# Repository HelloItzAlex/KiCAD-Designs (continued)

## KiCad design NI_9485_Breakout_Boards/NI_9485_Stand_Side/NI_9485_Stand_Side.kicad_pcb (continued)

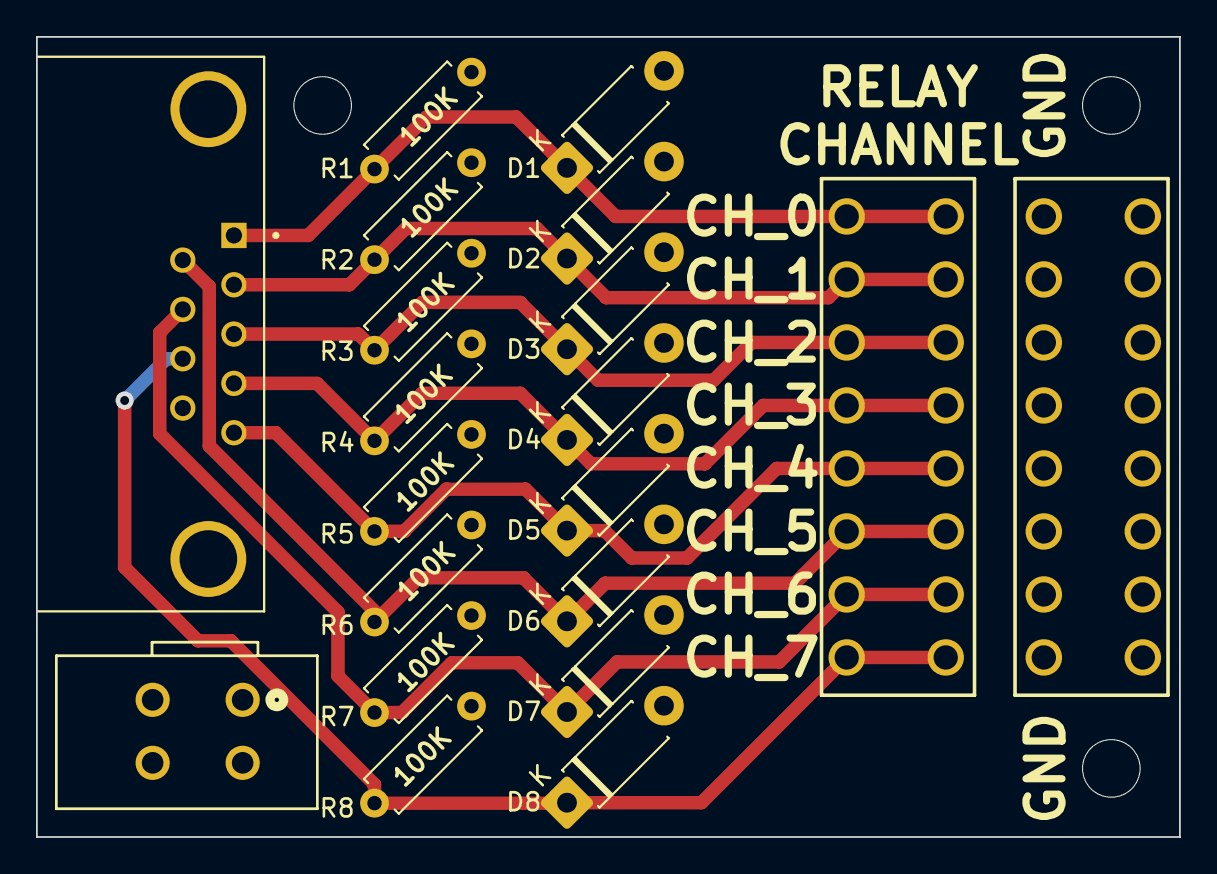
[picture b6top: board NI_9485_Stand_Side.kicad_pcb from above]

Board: 2 copper layers, 63.5 x 44.4 mm, 23 parts (0 on the bottom side), 9 nets.

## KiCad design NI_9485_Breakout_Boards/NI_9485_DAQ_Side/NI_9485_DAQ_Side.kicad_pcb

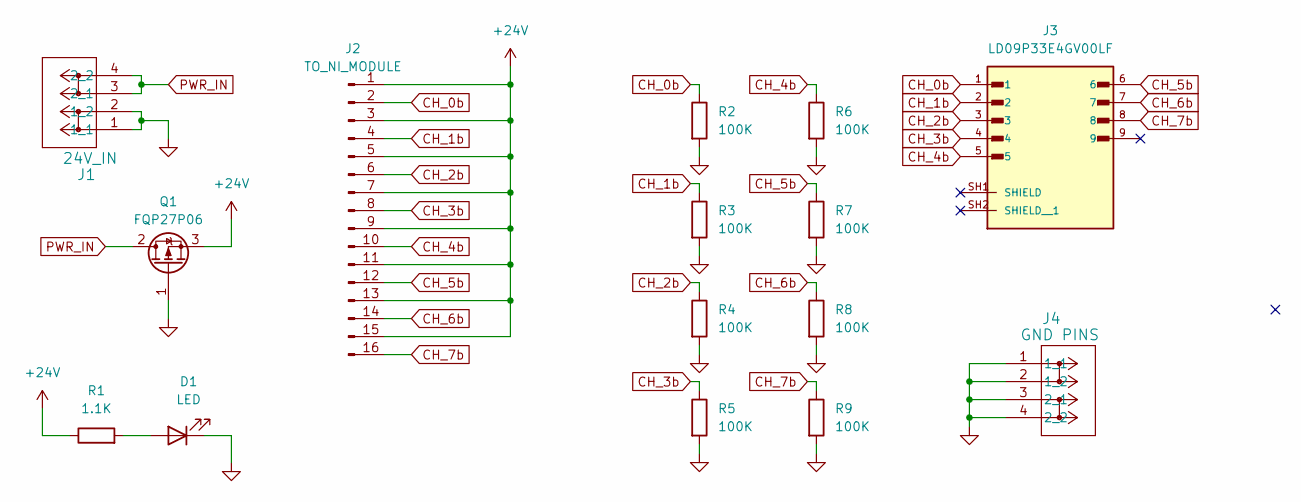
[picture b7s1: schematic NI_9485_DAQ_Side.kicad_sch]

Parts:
D1: LED; LED_D3.0mm_FlatTop
J1: 24V_IN; CONN2_2601-1102_WAG
J2: TO_NI_MODULE; 01x16 Horiz Pins
J3: LD09P33E4GV00LF; AMPHENOL_LD09P33E4GV00LF; PARTREV B
J4: GND PINS; CONN2_2601-1102_WAG
Q1: FQP27P06; TO-220-3_Vertical
R1: 1.1K; R_Axial_DIN0207_L6.3mm_D2.5mm_P7.62mm_Horizontal
R2, R3, R4, R5, R6, R7, R8, R9: 100K; R_Axial_DIN0207_L6.3mm_D2.5mm_P7.62mm_Horizontal

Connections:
+24V: J2.1, J2.3, J2.5, J2.7, J2.9, J2.11, J2.13, J2.15, Q1.3 (S), R1.1
CH_0b: J2.2, J3.1, R2.1
CH_1b: J2.4, J3.2, R3.1
CH_2b: J2.6, J3.3, R4.1
CH_3b: J2.8, J3.4, R5.1
CH_4b: J2.10, J3.5, R6.1
CH_5b: J2.12, J3.6, R7.1
CH_6b: J2.14, J3.7, R8.1
CH_7b: J2.16, J3.8, R9.1
GND: D1.1 (K), J1.1 (1_1), J1.2 (1_2), J4.1 (1_1), J4.2 (1_2), J4.3 (2_1), J4.4 (2_2), Q1.1 (G), R2.2, R3.2, R4.2, R5.2, R6.2, R7.2, R8.2, R9.2
unnamed: D1.2 (A), R1.2
PWR_IN: J1.3 (2_1), J1.4 (2_2), Q1.2 (D)

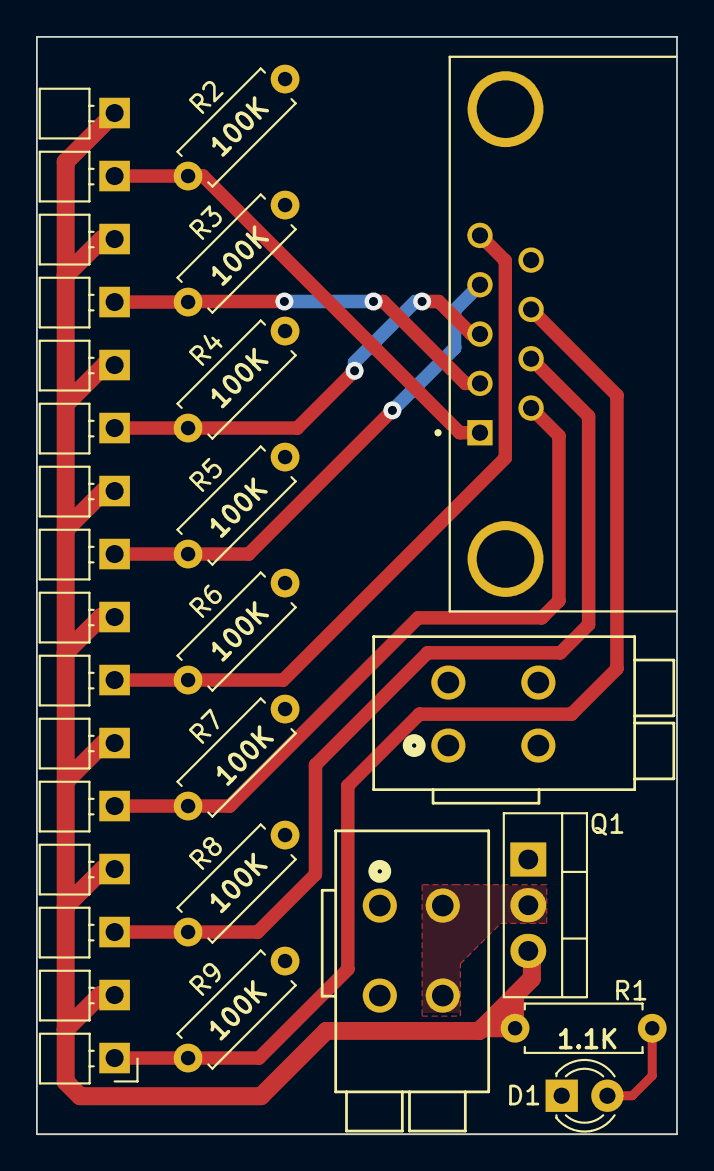
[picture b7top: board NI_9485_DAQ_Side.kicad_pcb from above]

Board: 2 copper layers, 35.6 x 61.0 mm, 15 parts (0 on the bottom side), 12 nets.

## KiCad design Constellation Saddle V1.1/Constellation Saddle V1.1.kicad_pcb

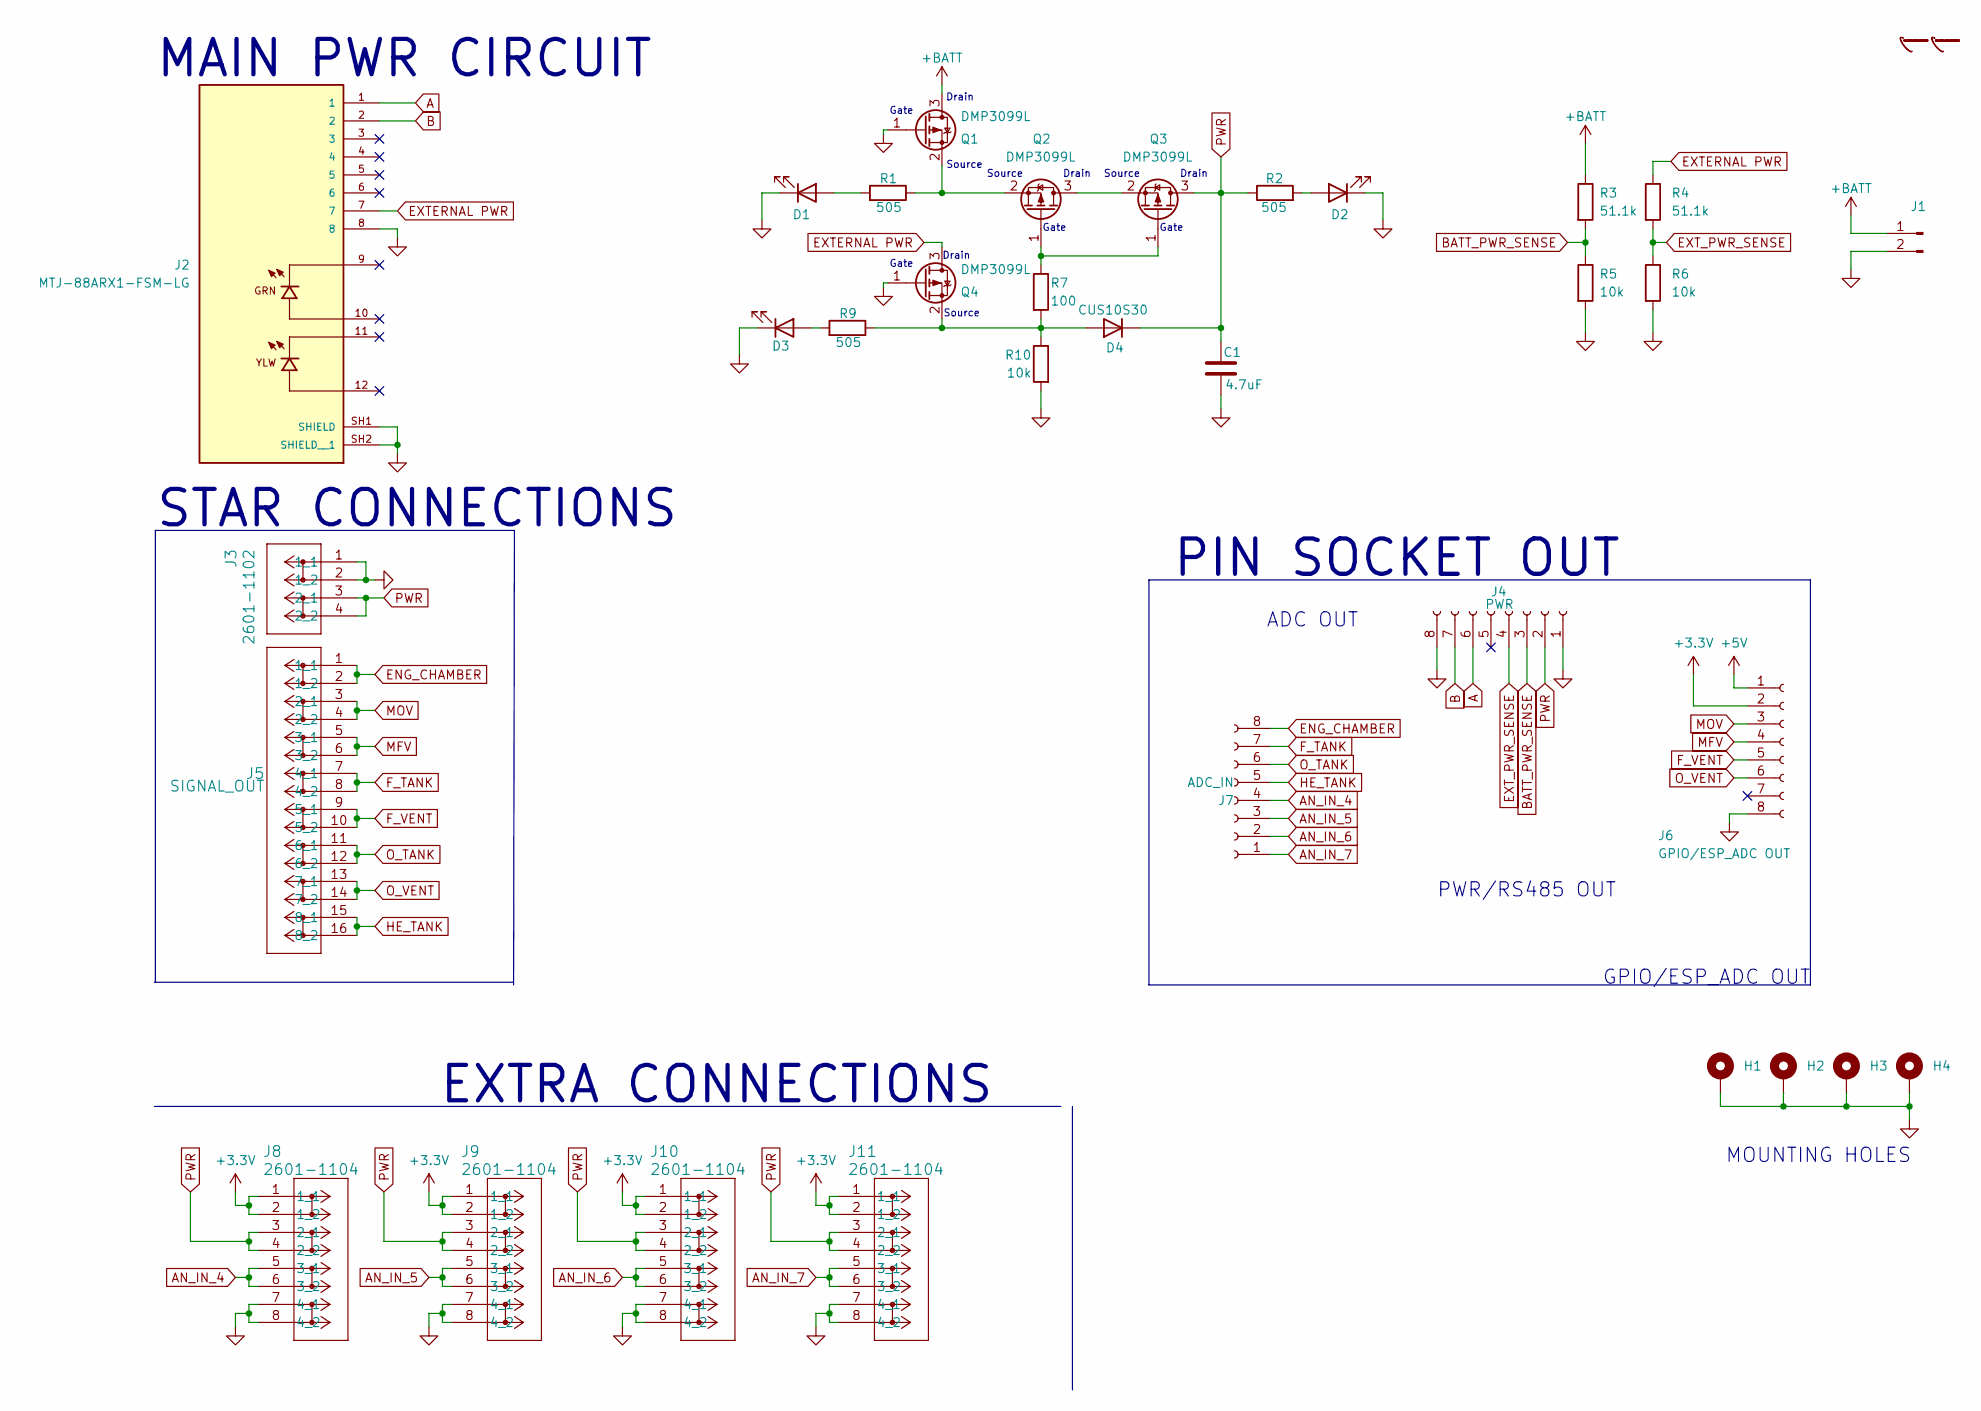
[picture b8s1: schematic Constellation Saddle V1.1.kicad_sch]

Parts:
C1: 4.7uF; C_0805_2012Metric
D1, D2, D3: LED; LED_0805_2012Metric
D4: CUS10S30; D_SOD-323
H1, H2, H3, H4: MountingHole_Pad; MountingHole_3.2mm_M3_DIN965_Pad
J1: Conn_01x02_Pin; SolderWire-0.75sqmm_1x02_P4.8mm_D1.25mm_OD2.3mm_Relief
J2: MTJ-88ARX1-FSM-LG; ADAMTECH_MTJ-88ARX1-FSM-LG; PARTREV H
J3: 2601-1102; CONN2_2601-1102_WAG
J4: PWR; PinSocket_1x08_P2.54mm_Vertical
J5: SIGNAL_OUT; CONN8_2601-1108_WAG
J6: GPIO/ESP_ADC OUT; PinSocket_1x08_P2.54mm_Vertical
J7: ADC_IN; PinSocket_1x08_P2.54mm_Vertical
J8, J9, J10, J11: 2601-1104; CONN4_2601-1104_WAG
Q1, Q2, Q3, Q4: DMP3099L; SOT-23-3
R1, R2, R9: 505; R_0805_2012Metric
R3, R4: 51.1k; R_0805_2012Metric
R5, R6, R10: 10k; R_0805_2012Metric
R7: 100; R_0805_2012Metric

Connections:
+3.3V: J6.2, J8.1 (1_1), J8.2 (1_2), J9.1 (1_1), J9.2 (1_2), J10.1 (1_1), J10.2 (1_2), J11.1 (1_1), J11.2 (1_2)
+5V: J6.1
+BATT: J1.1, Q1.3 (D), R3.1
A: J2.1, J4.6
AN_IN_4: J7.4, J8.5 (3_1), J8.6 (3_2)
AN_IN_5: J7.3, J9.5 (3_1), J9.6 (3_2)
AN_IN_6: J7.2, J10.5 (3_1), J10.6 (3_2)
AN_IN_7: J7.1, J11.5 (3_1), J11.6 (3_2)
B: J2.2, J4.7
BATT_PWR_SENSE: J4.3, R3.2, R5.1
ENG_CHAMBER: J5.1 (1_1), J5.2 (1_2), J7.8
EXTERNAL PWR: J2.7, Q4.3 (D), R4.1
EXT_PWR_SENSE: J4.4, R4.2, R6.1
F_TANK: J5.7 (4_1), J5.8 (4_2), J7.7
F_VENT: J5.9 (5_1), J5.10 (5_2), J6.5
GND: C1.2, D1.1 (K), D2.1 (K), D3.1 (K), H1.1, H2.1, H3.1, H4.1, J1.2, J2.8, J2.SH1 (SHIELD), J2.SH2 (SHIELD__1), J3.1 (1_1), J3.2 (1_2), J4.1, J4.8, J6.8, J8.7 (4_1), J8.8 (4_2), J9.7 (4_1), J9.8 (4_2), J10.7 (4_1), J10.8 (4_2), J11.7 (4_1), J11.8 (4_2), Q1.1 (G), Q4.1 (G), R5.2, R6.2, R10.2
HE_TANK: J5.15 (8_1), J5.16 (8_2), J7.5
MFV: J5.5 (3_1), J5.6 (3_2), J6.4
MOV: J5.3 (2_1), J5.4 (2_2), J6.3
unnamed: D1.2 (A), R1.2
unnamed: D2.2 (A), R2.2
unnamed: D3.2 (A), R9.2
unnamed: D4.2 (A), Q4.2 (S), R7.2, R9.1, R10.1
unnamed: Q1.2 (S), Q2.2 (S), R1.1
unnamed: Q2.3 (D), Q3.2 (S)
unnamed: Q2.1 (G), Q3.1 (G), R7.1
O_TANK: J5.11 (6_1), J5.12 (6_2), J7.6
O_VENT: J5.13 (7_1), J5.14 (7_2), J6.6
PWR: C1.1, D4.1 (K), J3.3 (2_1), J3.4 (2_2), J4.2, J8.3 (2_1), J8.4 (2_2), J9.3 (2_1), J9.4 (2_2), J10.3 (2_1), J10.4 (2_2), J11.3 (2_1), J11.4 (2_2), Q3.3 (D), R2.1

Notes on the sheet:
Gate
GPIO/ESP_ADC OUT
Drain
Source
MOUNTING HOLES
PWR/RS485 OUT
MAIN PWR CIRCUIT
ADC OUT
STAR CONNECTIONS
EXTRA CONNECTIONS
PIN SOCKET OUT

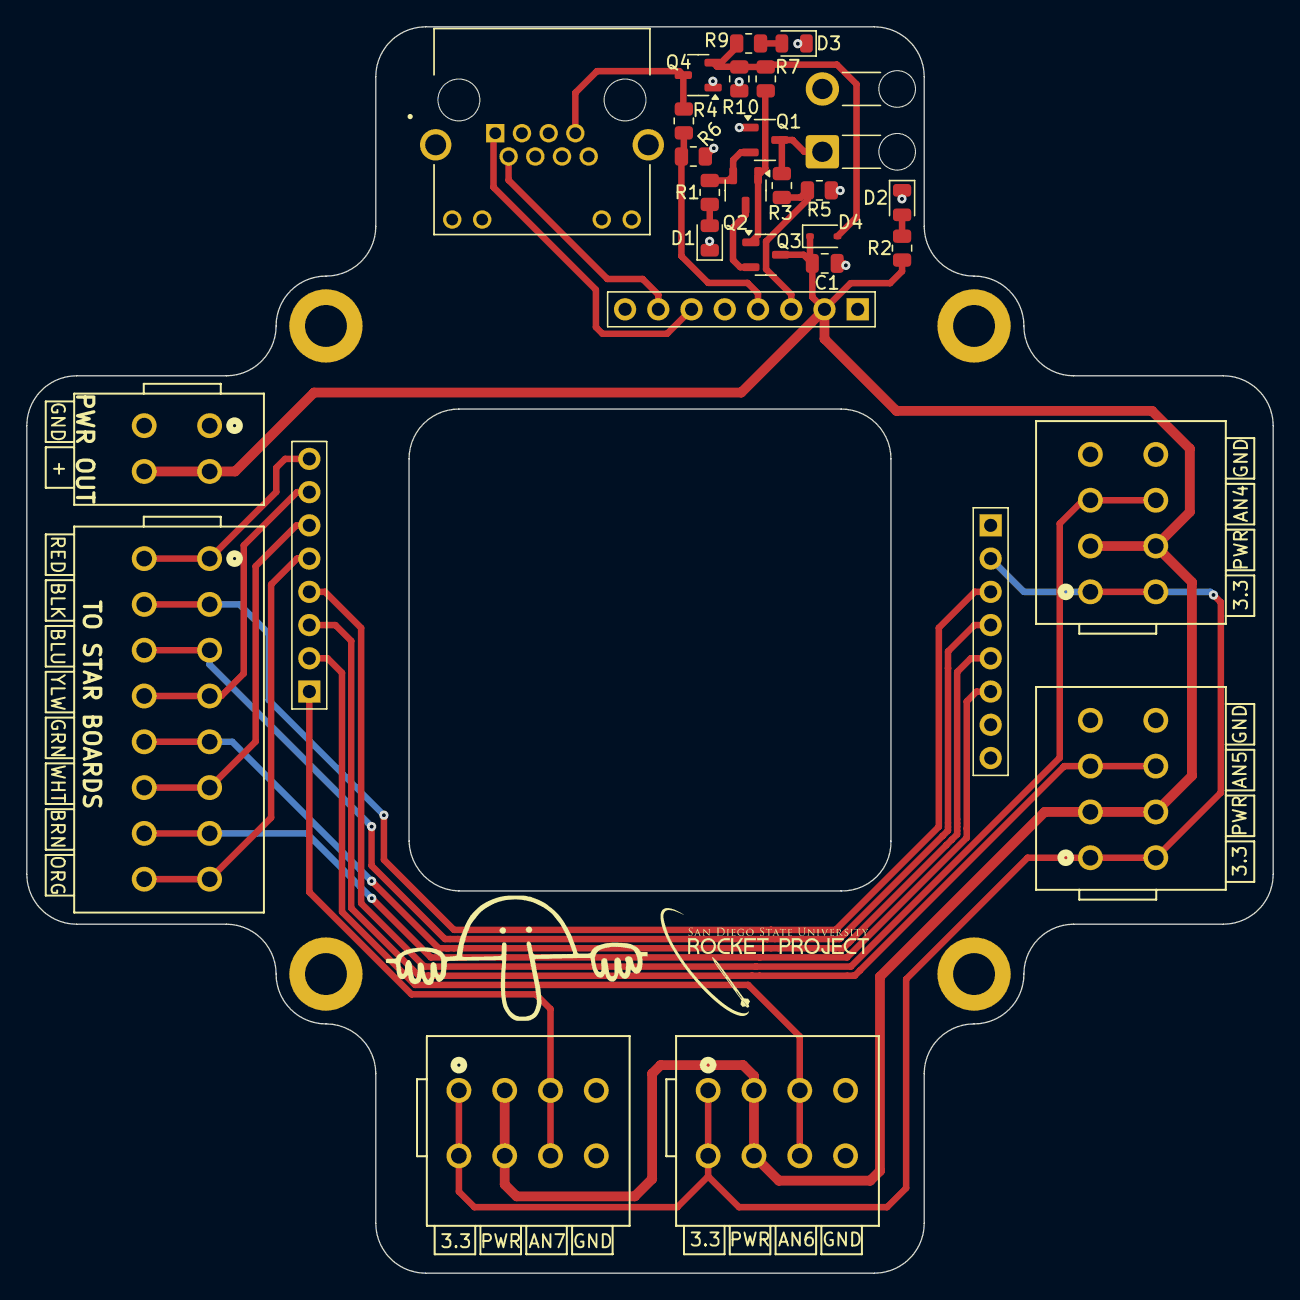
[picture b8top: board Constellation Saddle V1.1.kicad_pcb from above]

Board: 2 copper layers, 95.2 x 95.2 mm, 33 parts (0 on the bottom side), 28 nets.

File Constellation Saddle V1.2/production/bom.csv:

Designator,Footprint,Quantity,Value,LCSC Part #
C1,0805,1,4.7uF,
"D1, D2, D3",0805,3,LED,
D4,D_SOD-323,1,CUS10S30,
"H1, H2, H3, H4",MountingHole_3.2mm_M3_DIN965_Pad,4,MountingHole_Pad,
J1,SolderWire-0.75sqmm_1x02_P4.8mm_D1.25mm_OD2.3mm_Relief,1,Conn_01x02_Pin,
"J10, J11, J8, J9",CONN4_2601-1104_WAG,4,2601-1104,
J2,ADAMTECH_MTJ-88ARX1-FSM-LG,1,MTJ-88ARX1-FSM-LG,
J3,CONN2_2601-1102_WAG,1,2601-1102,
J4,PinSocket_1x08_P2.54mm_Vertical,1,PWR,
J5,CONN8_2601-1108_WAG,1,SIGNAL_OUT,
J6,PinSocket_1x08_P2.54mm_Vertical,1,GPIO/ESP_ADC OUT,
J7,PinSocket_1x08_P2.54mm_Vertical,1,ADC_IN,
"Q1, Q2, Q3, Q4",SOT-23-3,4,DMP3099L,
"R1, R2, R9",0805,3,505,
"R10, R5, R6",0805,3,10k,
"R3, R4",0805,2,51.1k,
R7,0805,1,100,

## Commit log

2023-02-21 Initial Create Attempt 1
2023-02-21 Added Arduino Nano
    LOL
2023-02-21 Added stuffs
2023-02-22 Almost done wiring BMI088
2023-02-22 Interrupts and Labels
2023-02-22 opened once
2023-02-22 New Attempt
2023-02-23 Open
2023-02-23 Idk man
2023-02-24 Some pins with capacitors
2023-02-24 more labels
2023-02-24 Open/No Changes
2023-02-27 Lots Of Changes
2023-02-27 Opened
2023-03-02 Programing Pins Added
2023-03-04 HSE crystal oscillator
2023-03-05 LSE Added
    Needs Phssst stuff
2023-03-08 Capacitor bank isolated
2023-03-15 Start in solenoid
2023-03-15 Attempted Solenoid valve
2023-03-18 Diode rotate
2023-03-20 Changed Solenoid Wiring
2023-03-22 Wired up solenoid stuff
    Not the circuits are there tho
2023-03-23 resistor added to ssr
2023-03-23 Lots of solenoids and pyro channels
2023-03-26 footprint
2023-03-27 PCB TIME
2023-03-27 Basic Pcb layout
2023-03-28 PCB work
2023-03-28 PCB Layout
2023-03-30 More PCB Work Might restart wiring
2023-03-31 Restart PCBdesign
    Why why why why why
2023-04-03 More work
2023-04-05 2 Layer Work
2023-04-06 Work
2023-04-06 Routing
2023-04-07 Ready for inspection
2023-04-07 Off to review
2023-04-07 Silk Screen
2023-04-08 Redesign the board
    Make smaller and look at notes
2023-04-08 Board size down
    NOW IS 2.25 X 4 INCHES EEEEK
2023-04-09 Done board
2023-04-09 BOM and Flip Prog pins
2023-04-09 Yas slay bom
2023-04-09 save
2023-04-19 BOM maneuvering
2023-04-19 Save 1
2023-04-20 New OBC Attempt Started
2023-04-20 Cherry Ref OBC
    Circle
2023-04-20 Transfer Parts
2023-04-22 Re org da files
2023-04-24 Work on board
2023-04-24 futz abt no changes
2023-04-24 close
2023-04-24 RCS gerbers
2023-04-24 AHHHHHHHH
    Have to redo all of the footprints haha
2023-04-24 footprint changes :sob:
2023-04-24 re did board footbrints
2023-04-25 push
2023-04-25 New Gerb
2023-04-26 Cherry Rework
2023-04-27 Pad Change
2023-04-28 Gerbs
2023-05-12 Rename Stuff
2023-05-13 Matcha V2
    2x2 inch 2 layer 4 solenoid sd longing trial board
2023-05-13 rOUND eDGES
2023-05-13 Slight Cosmetic Changes
2023-05-14 1x4 prog pins
2023-05-16 OBC Attempt 5
    2.25x2.25in 8 solenoid SD card logging board
2023-05-16 Some 4 Layer Work :)
2023-05-17 start over
2023-05-17 reorg mpu
2023-05-18 Cant move stuff
2023-05-19 Ahhhhh
2023-05-22 Proper 4 Layer Work
2023-05-23 Maybe Finished
    Maybe finished the 4 layer board but uhhh I need a check
2023-05-23 BAROMETER ADD
2023-05-23 Ground Systems Solenoid Board
    A board to replace the terminal blocks on the ground systems
2023-05-23 Thing
2023-05-24 Finished the Solenoid PCB
2023-05-25 Some Changes
2023-05-26 Some work
2023-05-26 PT Board Moment
2023-05-29 Working on schematic
2023-05-30 Complete chematic
    Might have to change the optocouplers
2023-05-31 Some late night pcb work
2023-05-31 Wired Everything in the board
2023-06-01 Added front stuff
2023-06-02 Open multiple
2023-06-02 no changes
2023-06-02 Idk lol some format changes
2023-06-05 Finished Wiring up OBC 7
2023-06-06 open once
2023-06-09 New Board for the Test Stand
2023-06-10 Changed the Switches
    Made a single switch to a single conn
2023-06-10 Created more banks
2023-06-11 Temp Foot Prints
2023-06-12 Ground System Work
2023-06-12 small work
2023-06-12 Shufflin around
2023-06-13 Reconfigured the LEDs
2023-06-13 Opened
    Reprints need silkscreen additions
2023-06-13 re config switches
2023-06-14 Added stitches
    Needs footprints made
2023-06-17 RFD900 Start
2023-06-17 added all the things for can
2023-06-18 Changed Test Stand GS
    Changed the gs schematic to reflect the current test box
2023-06-19 No work just opened kicad
2023-06-25 Re Done Power Supply Board
2023-06-26 AGS Board Work
2023-06-26 Power Line Changes
2023-06-28 Some Gerbs Some Work
2023-06-29 Reworked the solenoid board
2023-06-29 Solenoid Board Gerbs
2023-06-30 RFD900 Work
    Made the whole board
2023-06-30 Pt Board Gerbs
2023-07-01 Some misc work
2023-07-01 RFD900 Gerbs
2023-08-18 womp piush
2023-08-22 New boards
2023-08-22 mem board work
2023-08-23 Work in class
2023-08-23 Finished Quad SPI
    Needs:
    High Speed Clock
    CAN IC
2023-08-25 Added V1.1 of AGS Boards
2023-08-25 Changed all the things to 5mm pitch
    yuck big board be like
2023-08-28 Lots of schematic changes
2023-08-29 PCB layout time
2023-08-30 Started on pcb layout
2023-08-30 Layout work
2023-08-30 Lab Work
2023-08-30 No work donw
2023-08-31 Complete board
2023-09-01 Revisions
2023-09-02 Woek
2023-09-03 Revions and new board
2023-09-05 Added BOMS
    https://www.digikey.com/short/8btm0n25
2023-09-05 Revised good mems
    https://www.digikey.com/short/14vp1r7m
2023-09-07 Quick fixes
2023-09-11 Personal obc start
2023-09-11 OBC V1.1
2023-09-12 Personal Work
2023-09-12 Personal Altimeter
    Needs Radio Part
    Needs Pyro Channels
2023-09-12 Reworked schematic
2023-09-12 Sent
2023-09-12 Mosfets Required
2023-09-13 Got the mosfets
    Needs resistor values
2023-09-13 Yert
2023-09-14 Small move
2023-09-15 Started layout
2023-09-16 Made deployment board
2023-09-16 Finished Board
    Name: OH CHUTE!
2023-10-16 Load cell finished
2023-10-16 Small shuffle
2023-10-17 GERBS!
2023-10-18 Redone yeah
2023-10-23 Some personal pcb work
2023-10-23 RCS work
2023-10-23 created flower pot and worked on personal board
2023-10-25 Yart
2023-10-31 Perosnal work
2023-11-07 Ah
    Ah
2023-12-02 Some more files
2023-12-18 2 new projects
2023-12-21 Analog stand stuffs
2023-12-21 Train work
2023-12-22 Lab jack work
2023-12-30 RocketBeacon files
2024-02-04 Breakout board work
2024-02-06 Raven Breakout
2024-02-07 Raven expansion
2024-03-06 AAAAA
2024-03-09 LP 16
2024-03-12 AAAAAAAAAA
2024-03-24 EEEEE
2024-03-27 Piss nugets
2024-03-27 Lots of things
2024-04-02 Piss
2024-05-09 New PT Board
2024-06-03 Boards
2024-06-03 AAAAAA
2024-07-15 Piss bot
2024-07-17 AAAA
2024-07-17 Bruhg
2024-07-20 AAAAAAAAA
2024-07-22 Personal OBC Layout
2024-07-29 AAAAaaaa
2024-08-12 LAF Board Work
2024-08-12 LAF Proto
2024-08-21 LAF Board Work
    Needs comm ICs
2024-08-29 Almost done
2024-08-30 No work
2024-09-03 ADC work
2024-09-03 Schem work
2024-09-04 Schematic done
    Needs cleaning up last bits of wiring and layout
2024-09-05 Layout has begun
2024-09-09 OBC Work
    Schematic 95% done
    Layout 75% done
2024-09-10 HAHAHA
2024-09-10 Psuh
2024-09-26 LAF board works
2024-10-01 ACS board changes
2024-10-04 EEEErrrr
2024-10-23 What then
2024-11-04 Rename
    LAF Proto to Constellation Stack
2024-11-04 Work today
2024-11-05 nothing
2024-11-07 Ahhh
2024-11-12 eEE errr
2024-11-13 Constella boards
2024-11-22 Stella boards
2024-11-22 AhhhhAhahahaha
2024-11-24 Ahahahaha
2024-11-24 Ahahahahaha
2024-11-24 Constella V2.0 Work
2024-11-26 Lots of STAR Boards
2024-11-27 GERBS MADE
2024-12-06 Constella
2024-12-11 Ahhhahahaha
2024-12-11 Erre r
2024-12-30 Ye haw looking 2.0
2025-01-10 69 changes
2025-01-14 Saddle
2025-01-17 V2.0 changes
2025-01-17 Kicad
2025-01-31 SOme stuff
2025-02-01 Eee rr
2025-02-05 3.0 time
2025-02-11 3.0 work
2025-02-14 3.0 stack
2025-02-21 HAHAHAH
2025-02-22 HEHEHHA
2025-02-22 Aaawwww yeah 90% done
2025-03-01 All the 3.0 files
2025-03-23 No wayayaya
2025-05-19 New LabJack PCB
2025-05-19 DB37
2025-07-03 NI_9485 Board
2025-07-04 New push
2025-07-04 Ni breakout
2025-07-07 kkkkkkkkkkkkkk
2025-07-13 Aaahaha
2025-08-04 AGS PCBS
2025-08-06 Producation files
2025-09-10 Stuff
2026-02-02 USB boards
2026-02-02 Kicand
